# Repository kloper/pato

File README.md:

# Pato is a HD44780 display driver for Atmel's megaAVR.

Pato turns Arduino Pro Mini (or any other Atmega based board) and its
attached HD44780-based display into printf() machine with small
subset of VT100 controls.

| New Stuff!!
| :----------
| I have just completed USI I2C driver for Attiny2313.
| The chip has very small amount of flash, so I was unable to pack
| the printf API in. Nevertheless, the direct HD44780 API works pretty
| well.

## Yet another Arduino library?

Pato is *NOT* Arduino display driver library. If you need
one, just google it - you will probably find the LiquidCrystal for
Arduino. Use it, it is great!

Pato is for those who want to save their valuable i/o pins, flash and
RAM memory and offload all the display-related functionality to a
separate processor. Pato provides free, open source display driver for
relatively cheap Atmel microprocessors.

This said, Pato actually contains HD44780 driver that can be used in
Arduino sketches. It is written in assembly and optimized to use minimal
amount of flash memory (208 bytes .text code segment size in hd44780.o) and
have small stack footprint (3 nested calls maximum).

Pato aims to be an all-in-one solution that integrates different software
components:

 * HD44780 display driver - provides access to the basic display API
 * Communication drivers - UART or I2C (TWI in Atmel terms)
 * Output buffering. Pato stores text to be displayed in memory and allows
   delta modifications only for parts that should change.   
 * String formatting - based on printf library from Atmel. This
   feature is optional and depends on amount of flash memory available
   on specific chip.
 * VT100 terminal controls support. Right now only basic control characters
   are supported.

## Hey, I can get such a thing on eBay for a buck!

Sure there are other similar solutions. Cheap ones provide only
core functionality, allowing to reduce number of i/o pins used to
drive the display, but software driver is still supposed to be a part
of the main processor firmware. More sophisticated solutions, that are
able to perform string formatting and terminal management are much more
expensive and are often closed source.

## What chips are supported?

My initial goal was to drive the display with Arduino Pro Mini that
can be found on eBay for a few bucks. Thus, Atmega328 and Atmega328p are
supported. Atmega2560 is supported too. 

In fact, porting to any Atmega is trivial, provided it has enough flash
memory, RAM, i/o pins and UART/TWI compatible with Atmega328.

I2C for Attiny2313 is supported but I still consider it experimental.

## License

BSD License. See LICENSE.md for more info.

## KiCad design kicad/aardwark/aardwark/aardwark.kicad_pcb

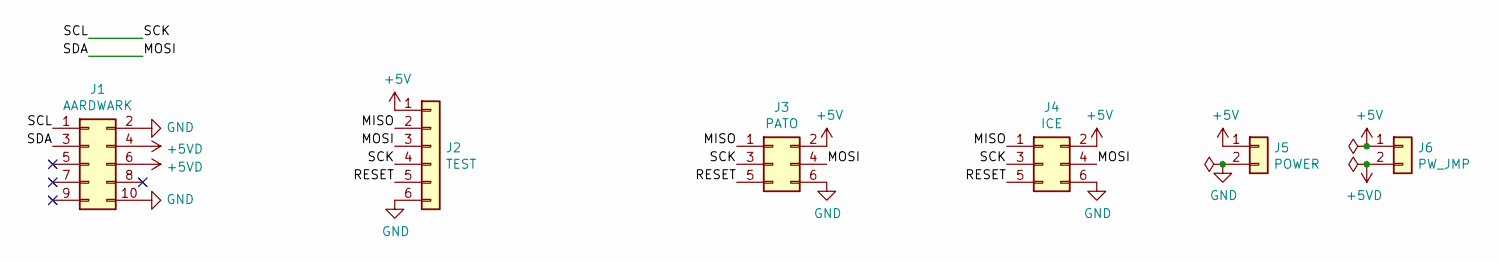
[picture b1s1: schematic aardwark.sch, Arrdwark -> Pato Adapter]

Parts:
J1: AARDWARK; Pin_Header_Straight_2x05_Pitch2.54mm
J2: TEST; Pin_Header_Straight_1x06_Pitch2.54mm
J3: PATO; Pin_Header_Straight_2x03_Pitch2.54mm
J4: ICE; Pin_Header_Straight_2x03_Pitch2.54mm
J5: POWER; Pin_Header_Straight_1x02_Pitch2.54mm
J6: PW_JMP; Pin_Header_Straight_1x02_Pitch2.54mm

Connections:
+5V: J2.1, J3.2, J4.2, J5.1, J6.1
+5VD: J1.4, J1.6, J6.2
/MISO: J2.2, J3.1, J4.1
/MOSI: J1.3, J2.3, J3.4, J4.4
/RESET: J2.5, J3.5, J4.5
/SCK: J1.1, J2.4, J3.3, J4.3
GND: J1.2, J1.10, J2.6, J3.6, J4.6, J5.2

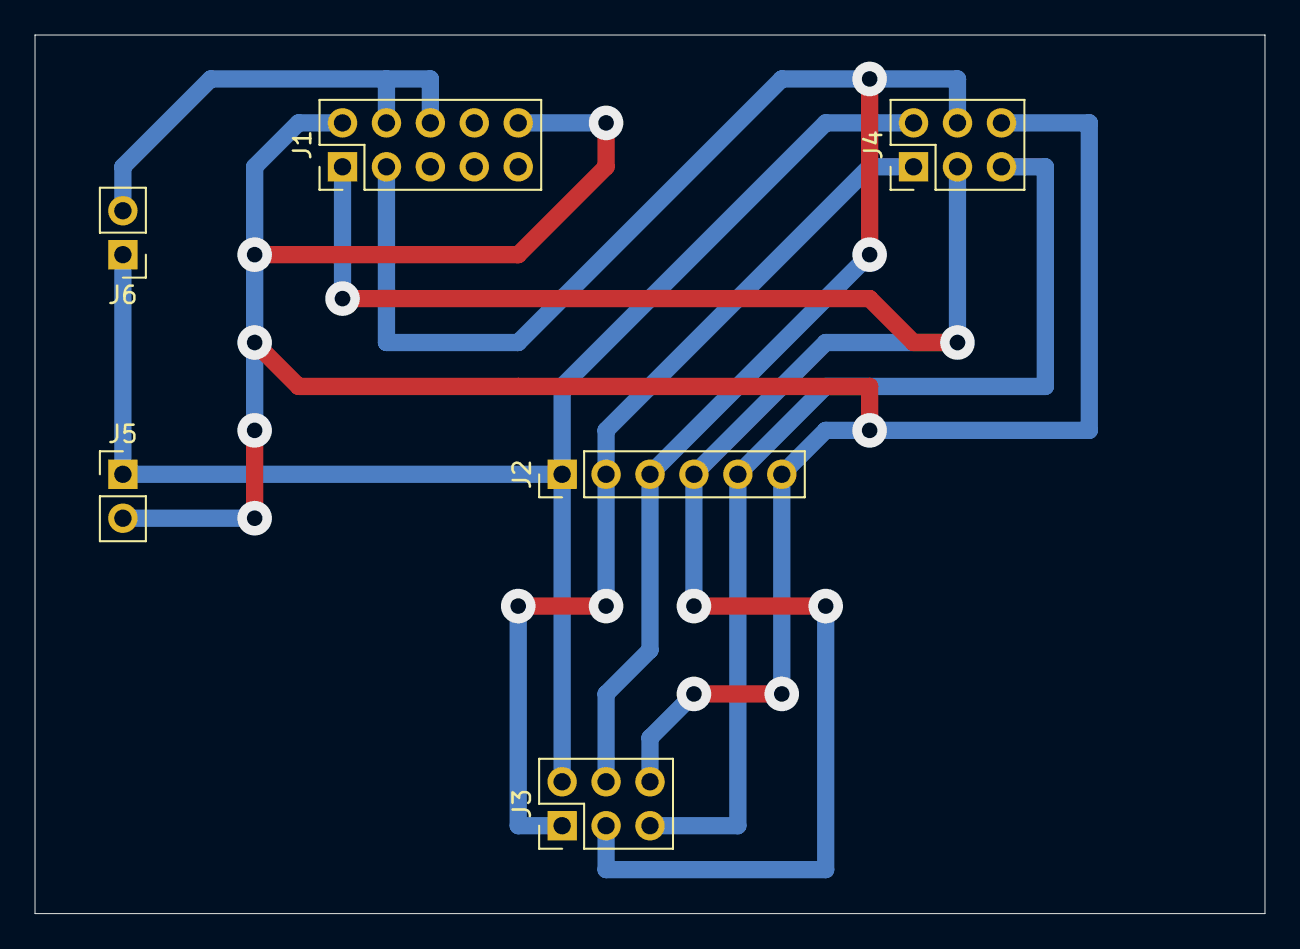
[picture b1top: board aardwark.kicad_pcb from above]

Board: 2 copper layers, 71.1 x 50.8 mm, 6 parts (0 on the bottom side), 7 nets.

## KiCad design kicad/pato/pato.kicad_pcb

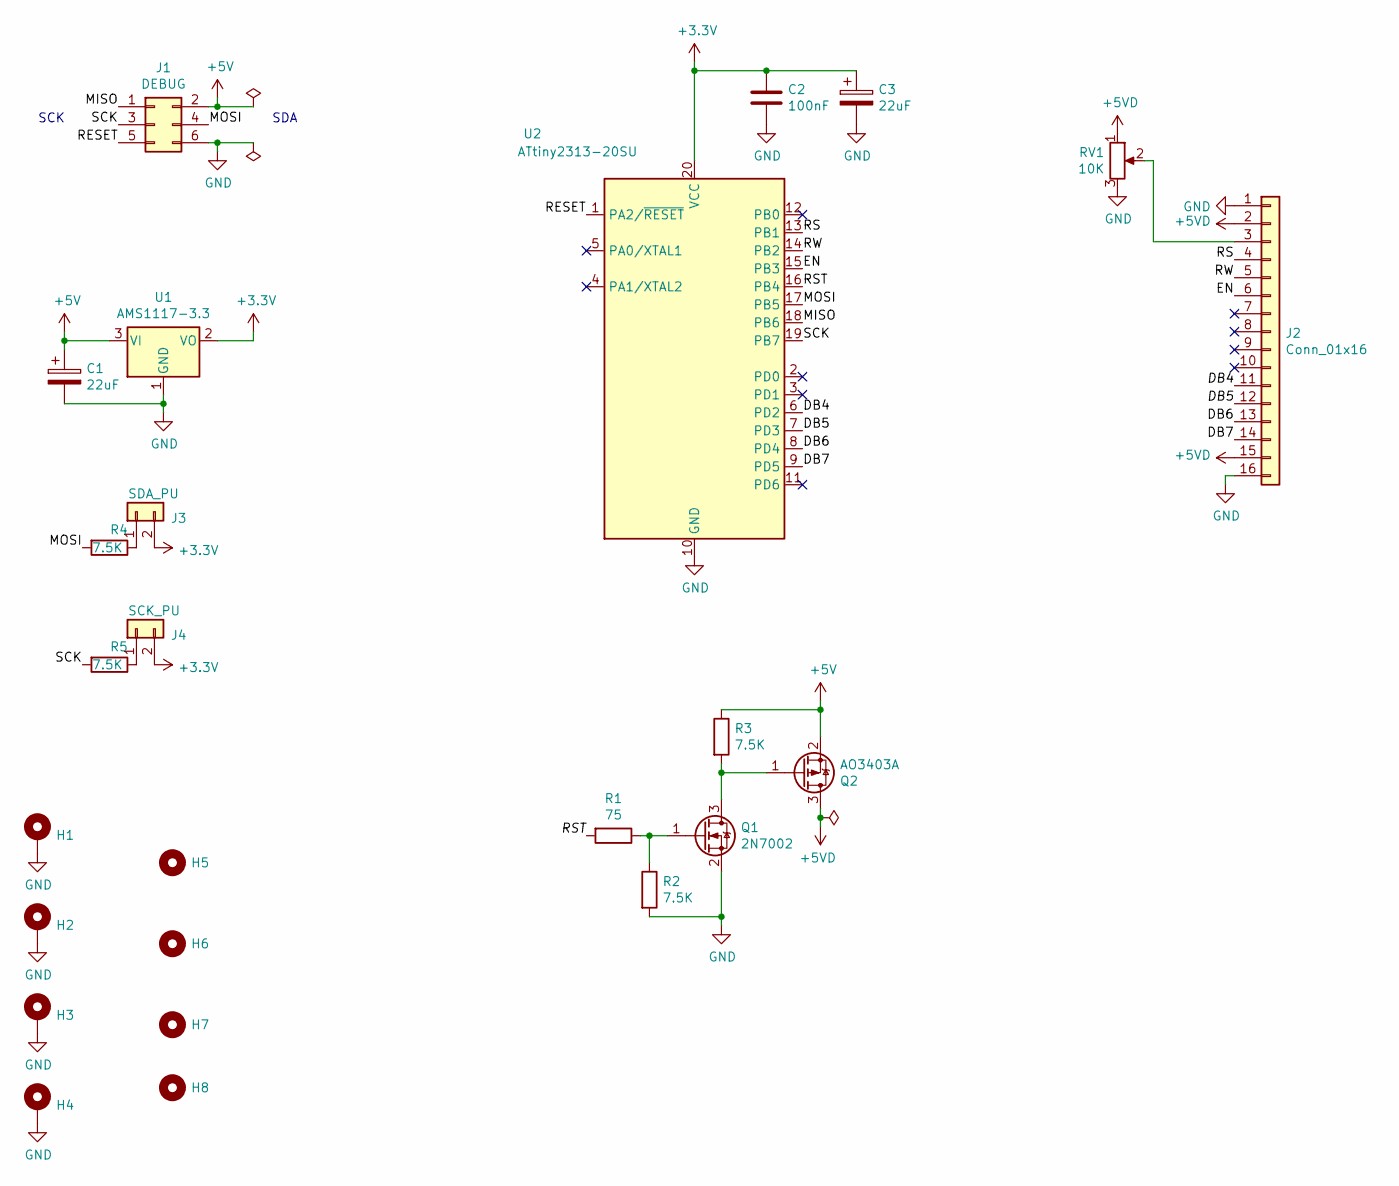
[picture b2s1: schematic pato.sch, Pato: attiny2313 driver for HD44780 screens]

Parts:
C1, C3: 22uF; CP_Tantalum_Case-X_EIA-7343-43_Hand
C2: 100nF; C_0603_HandSoldering
H1, H2, H3, H4: MountingHole_Pad; MountingHole_3.2mm_M3_Pad
H5, H6, H7, H8: MountingHole; MountingHole_3.2mm_M3
J1: DEBUG; Pin_Header_Straight_2x03_Pitch2.54mm_SMD
J2: Conn_01x16; Pin_Header_Straight_1x16_Pitch2.54mm
J3: SDA_PU; Pin_Header_Straight_1x02_Pitch2.54mm
J4: SCK_PU; Pin_Header_Straight_1x02_Pitch2.54mm
Q1: 2N7002; SOT-23
Q2: AO3403A; SOT-23
R1: 75; C_0805_HandSoldering
R2, R3, R4, R5: 7.5K; C_0805_HandSoldering
RV1: 10K; Potentiometer_Trimmer_Bourns_3005
U1: AMS1117-3.3; SOT-223-3_TabPin2
U2: ATtiny2313-20SU; SOIC-20W_7.5x12.8mm_Pitch1.27mm

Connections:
+3V3: C2.1, C3.1, J3.2, J4.2, U1.2 (VO), U2.20 (VCC)
+5V: C1.1, J1.2, Q2.2 (S), R3.1, U1.3 (VI)
+5VD: J2.2, J2.15, Q2.3 (D), RV1.1
/DB4: J2.11, U2.6 (PD2)
/DB5: J2.12, U2.7 (PD3)
/DB6: J2.13, U2.8 (PD4)
/DB7: J2.14, U2.9 (PD5)
/EN: J2.6, U2.15 (PB3)
/MISO: J1.1, U2.18 (PB6)
/MOSI: J1.4, R4.2, U2.17 (PB5)
/RESET: J1.5, U2.1 (PA2/~RESET)
/RS: J2.4, U2.13 (PB1)
/RST: R1.2, U2.16 (PB4)
/RW: J2.5, U2.14 (PB2)
/SCK: J1.3, R5.2, U2.19 (PB7)
GND: C1.2, C2.2, C3.2, H1.1, H2.1, H3.1, H4.1, J1.6, J2.1, J2.16, Q1.2 (S), R2.2, RV1.3, U1.1 (GND), U2.10 (GND)
unnamed: J2.3, RV1.2
unnamed: J3.1, R4.1
unnamed: J4.1, R5.1
unnamed: Q1.1 (G), R1.1, R2.1
unnamed: Q1.3 (D), Q2.1 (G), R3.2

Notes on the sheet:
SDA
SCK

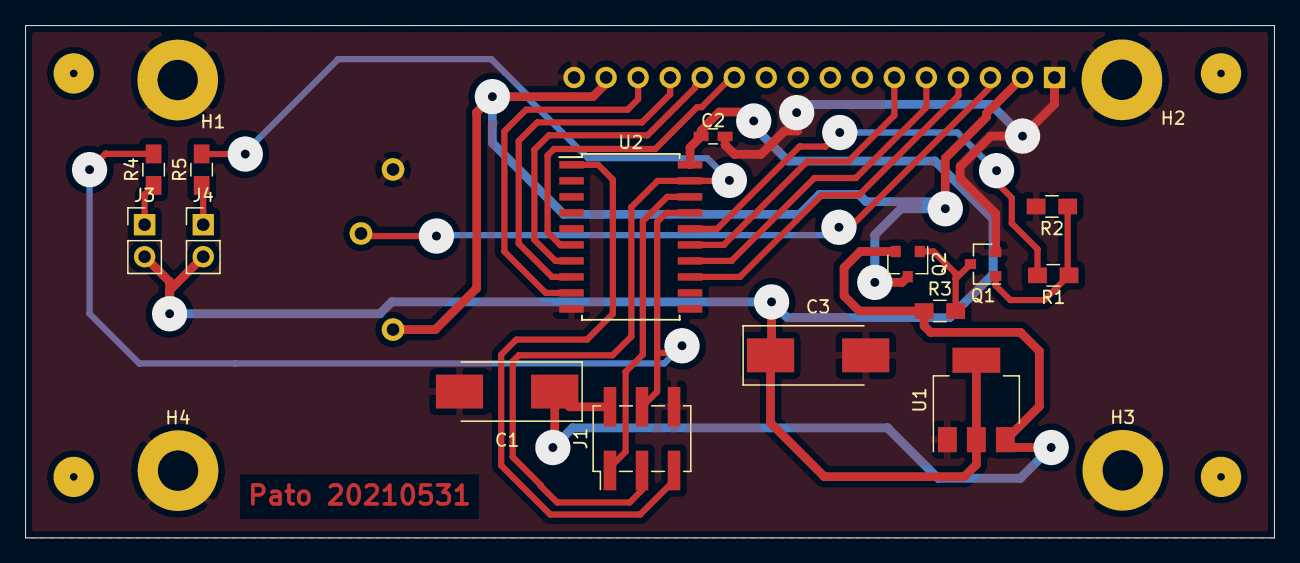
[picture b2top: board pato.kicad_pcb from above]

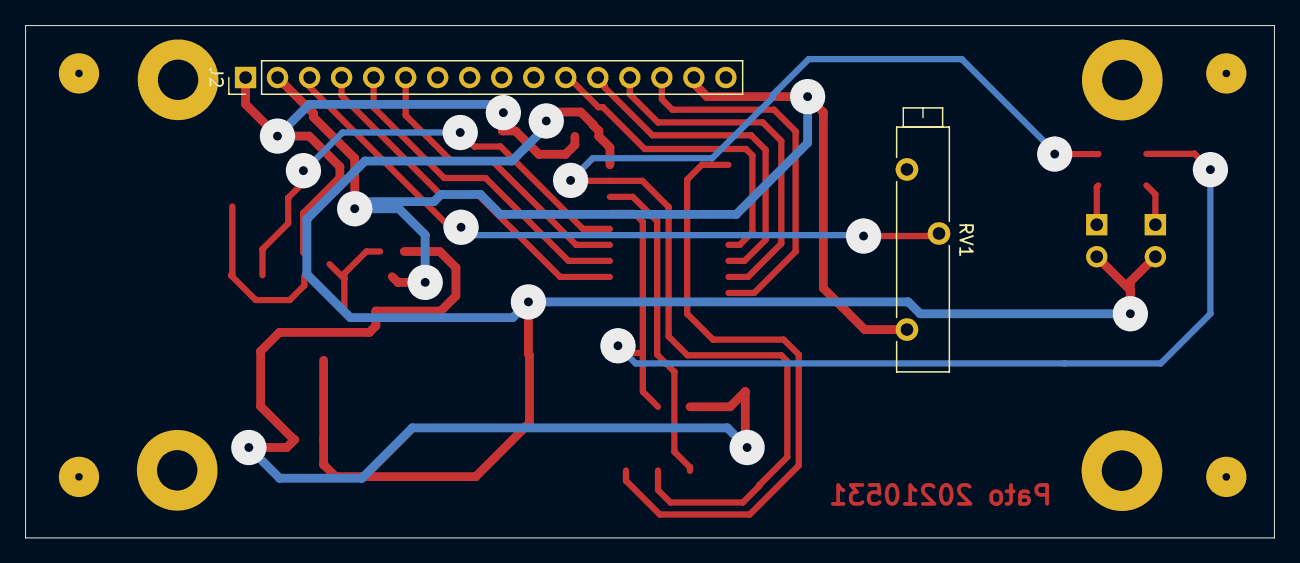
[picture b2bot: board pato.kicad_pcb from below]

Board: 2 copper layers, 99.1 x 40.6 mm, 25 parts (2 on the bottom side), 21 nets.

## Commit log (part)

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2014-12-24 Initial import of HT44780 driver.
    Current version is developed on atmega2560.
2014-12-28 First implementation for simple UART interface.
2014-12-28 Import of .gitignore file.
2014-12-28 Reimplement UART ISR using assembly for smaller stack footprint.
2015-01-01 Implemented main loop for pato and basic commands.
2015-01-01 Fix bad reset value.
    The initial reset value set 4-bit-bus value as HIGH instead of LOW.
2015-01-01 Fix Pato.execute() to not expect reply after RESET.
2015-01-01 Fix Read reply parser to return both address and read data.
2015-01-01 Implement test_read, that invokes reset, ddaddr and other, except read.
2015-01-01 Change hd44780_reset() to accept special value 0xff as shutdown flag.
2015-01-01 Make nibble_in and nibble_out functions instead macros.
    This will save place in .text segment.
2015-01-01 Remove unneeded comments.
2015-01-04 Implement first version of buffered output to the display.
    The current version keeps 80-byte buffer that is used to pass parameters to vfprintf()
    function. The buffer can be modified by means of print_setaddr(), print_put() commands.
    It can be flushed to the screen using print_commit() command.
2015-01-04 Fix print_put() and print_commit() functionality.
    There was a single bug - commit didn't increment pointer to zero character,
    thus extra zero was encountered in the first vfprintf() parameter.
2015-01-09 First naive but working version of terminal code.
2015-01-09 Make more generic implementation for cursor navigation.
    This is needed for future terminal control sequences and bidi support.
2015-01-15 Fix firmware/crc.c header.header
2015-01-15 Remove extra empty lines.
2015-01-15 Introduce UART<->I2C bridge for testing I2C stuff in Pato.
2015-01-15 Moved crc.py to util package
2015-01-15 Fix pato code to use util.crc
2015-01-16 Make size op packet to be a first field of packet header.
    While using COBS size field is not needed since each packet is delimited.
    The problem arises on Windows side, since serial port API (encapsulated by
    pyserial) does not have "read till zero" API (or at least I didn't found
    one). Thus when receiving COBS packets on Windows I need either to spend
    some time for timeout, use fixed size packets or check packet lengthes.
2015-01-16 Fixes in UART interface.
    uart_recv() does not return pointer to the input buffer, instead a
    special function uart_inbuf() is used.
2015-01-16 Eliminate use of temp variables in UART ISR since they are compiled out causing problems.
2015-01-16 Temporarily switched bridge to atmega2560.
2015-01-16 Fixed imports.
2015-01-16 Removed extra empty line.
2015-01-16 Introduce COBS encoding to make UART packets zero delimited.
2015-01-16 Introduce bridge protocol and driver.
2015-01-23 Make cobs_encode() accepted size consistend with size of actual data including the leading pad byte.
2015-01-23 Fix missing import.
2015-01-23 Introducing python interface to the bridge including some tests.
2015-01-25 Remove attiny2313 from config and split 328 config into 328 and 328p.
    The former one is used for development on stk500.
2015-01-25 Add fixed timeout for twi_wait().
    The timeout is managed by WatchDog Timer in interrupt mode.
2015-01-25 Improved tracing a little bit.
2015-01-27 Send I2C STOP on timeout if needed.
2015-01-29 Introduce TWI slave driver for pato.
2015-01-31 Make UART and TWI mutually exclusive in respect to the main loop functionality.
    Make also uneeded communication protocol to be compiled out.
2015-01-31 Fix TWI driver to reset TWINT on each action.
    Also TWEA must be set for all states except thos explicit ones that NACK is required.
2015-01-31 Extra test for checking bridge-pato communication.
2015-02-05 Add check for incoming packet last byte to be zero.
    The twi/uart set that byte to non-zero value before receive.
    So we are actually sure we did receive something when it is zero.
2015-02-05 Move send/receive client functionality out of pato protocol to specific transport classes.
2015-02-05 Split test class into two separate classes sharing same set of tests.
    One class per transport type (I2C, UART). Add extra tests for the new I2C protocol.
2015-02-06 Solution change allowing TWI debugging.
2015-02-12 Fix file headers to have proper BSD license.
2015-02-12 Check "preserve EEPROM" on erase option in the projects.
2015-02-12 More ignored stuff for git.
2015-02-18 Fixes for actually running Pato on Atmega328
2015-02-18 Introducing first version of doxygen config for Pato.
2015-02-21 Wrote documentation for HD44780 low level interface.
2015-02-26 More documentation on Pato's protocol.
2015-02-28 More documentation for CRC and fix brief string of print.c
2015-03-03 Make main request and reply pointers volatile to eliminate compiler quircs.
2015-03-03 Switch bridge to atmega328p.
2015-03-03 Fix TWI ISR wrong status assignment on status 0xA0.
2015-03-03 Add performance counters for debugging.
2015-03-07 Remove long delays in nibble_in/nibble_out functions.
    Looks like I did wrong math when looked on HD44780 timing diagrams.
2015-03-07 Fix RESET command misbehavior when it was disruped by interrupts.
    Now guarding on hd44780_reset() using cli()/sei() pair.
2015-03-07 Fix TWI hangouts when master make write and read while write without stop confition.
    In such a situation slave "knows" about write completion too late (upon receiving 0xA0
    at the beginning of the read). This leads to missing read and later to missing write from
    master.
    In order to fix that I have made slave code to exit from twi_slave_wait() upon receiving of
    the packet without regard to stop condition. The TWINT flag is not cleared so muster must
    wait for packet processing completion.
2015-03-07 Make bridge ping test to not fail on errors, just report ones.
2015-03-09 Ignore doxygen output
2015-03-09 Introduce HAVE_PRINTF configuration define.
    If defined, Pato will use Atmel's printf library for
    output formatting. This will make larger code with nice
    formatting features. With HAVE_PRINTF undefined Pato
    will treat print buffer as a string without applying any
    formatting.
2015-03-09 Introduce HAVE_PRINT configuration define.
    When defined the print API is compiled in. Otherwise it is compiled out.
2015-03-11 Started attiny2313 porting.
2015-03-13 Performance optimization for communication with HD44780.
    Reimplemented communication functions to be less dependent on SBI and CBI
    instructions. This implies using IN and OUT instructions on the entire
    data port in READ-MODIFY-WRITE fashion. This is not interrupt safe if
    future ISRs will reuse remaining pins in the data port.
2015-03-13 Link with -lprintf_flt to test floating point number functionality of printf library.
    Added a new test for that.
2015-03-14 Introduced ToDoList task list for issue management.
2015-03-16 Implement additional control characters.
    In addition to ealready implemented '\n', '\f', '\b' added '\t', '\v', '\r' and
    started to implement '\e' (ESC)
2015-03-16 Fix "index out of range" exception in bridge packet parser
    This happens when bridge.protocol.packet tests packet for error response.
    Since packet can be small and not have 5 elements this will throw since
    assertTrue() is a method and evaluates its parameters before invocations.
2015-03-16 Clean up in the test stuff
    Moved common stuff to other modules, refactored logging and common functions.
2015-03-23 Introduced Arduino library for easy communication with Pato
2015-03-23 Extended the Arduino library with direct HD44780 functionality.
2015-03-31 Introduced the print API for Arduino library for pato and the corresponding sample sketch.
    It is still work in progress since "printf" interface requires special handling
    of %s parameters.
2015-03-31 README update.
2015-03-31 Print API changes
    1. Created print_put_ptr() command that takes offset insde of the print buffer.
    It turns that offset to a real pointer and saves it at the current
    print address as print_put() do. This is done to handle "%s" format strings
    that require both string and pointer to it to be present in the print buffer.
    2. The print_commit() now takes offset as a parameter that determines where
    parameters for printf() are started.
2015-03-31 Arduino library changes following the protocol changes
2015-04-01 Fix printf() argument position calculation in print_commit()
2015-04-01 Turn print statement invocation into function invocation.
    This is for future python 3 switch.
2015-04-01 Minor. Change COM port for bridge.
2015-04-01 Fix python code to reflect recent changes in print protocol.
2015-04-10 Move all advanced Pato::print() stuff to a separate file.
    The simplified c++ interface for Arduino was moved to
    arduino/pato/pato/print.h. The interface was changed to handle strings
    well and is implemented as a set of functions with interface similiar to
    fprintf().
2015-04-10 Support up to 5 data arguments for pato::print()
2015-04-14 Add brief descriptions for modules.
2015-04-14 Python code documentation updates + refactorings required to make pylint happy.
2015-04-14 TODO update.
2015-04-20 More documentation under pato.protocol + pylint fixes.
2015-04-20 Documengtation and pylint fixes under pato.transport
2015-04-26 Documengtation and pylint fixes under bridge.*
2015-04-27 Fix broken tests + minor pylint fixes in test code.
2015-04-30 Fix tty_state.skip_til_nl surviving display reset.
    The state variable was not reset by display resetting. This is wrong in scenario
    when printing line without \n, resetting display and printing a line again.
    The second line is not printed since skip_til_nl is set to true.
    Introduced hd44780_print_reset() that is called on display reset.
2015-05-02 Put all configuration variables in a structure.
    Pato is based on EEPROM-based configuration variables. Since order of
    the variables in EEPROM depends on compiler version it is hard to automate
    EEP file creation.
    Fixed that by putting all the variables in pato_config_t structure.
2015-05-02 Make doxygen to output warning long.
2015-05-02 TODO update
2015-09-22 Add Release subdir to gitignore
2015-09-22 Port timeout functions to attiny2313
    It seems like on attiny2313 TIFR0 register is out of reach of sbi*
    commands (register number greater than 32 or so).
    This change switches from SBI to STS command and SBIC to an
    equivalent equivalent sequence of LDS and SBRC.
2015-09-22 Make timeout functions block interrupts
    This is done to prevent interrupt bombing when frequent interrupt
    just keeps the function to complete in time.
2015-09-22 Implement USI I2C driver for attiny2313
2015-09-22 Fix README to have information about attiny2313. Spell check it finally.
2021-05-29 Change REPLY_OK value to 0xfe ...
    To be easy recognizable in tracing
2021-05-29 Fix display sequence to match HD44780 spec
2021-05-29 Fix USI code to actually work with Attiny2313
2021-05-29 Automatic upgrade to a modern Microchip (Atmel) Studio.
2021-05-29 Upgrade to python 3 + Support TotalPhase Aardwark as a transport
2021-05-29 Introducing kicad project for pato with 1602 display
2021-05-31 Introduce HAVE_PRINT_MINMAL ...
    It allows tty print functionality, but reduces some features
2021-05-31 Add config and EEPROM defaults for 1602 screen
2021-05-31 Disable Aardwark pullups since it does not power pato
2021-05-31 Add fill test to check depth of display memory
2021-05-31 Add on-board pull-up option
2021-05-31 Add pinouts on F.Fab layer for Aardwark adapter

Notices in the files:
kicad/pato/pato.kicad_pcb:
Simpified BSD License
kicad/pato/pato.sch:
Simplified BSD License
